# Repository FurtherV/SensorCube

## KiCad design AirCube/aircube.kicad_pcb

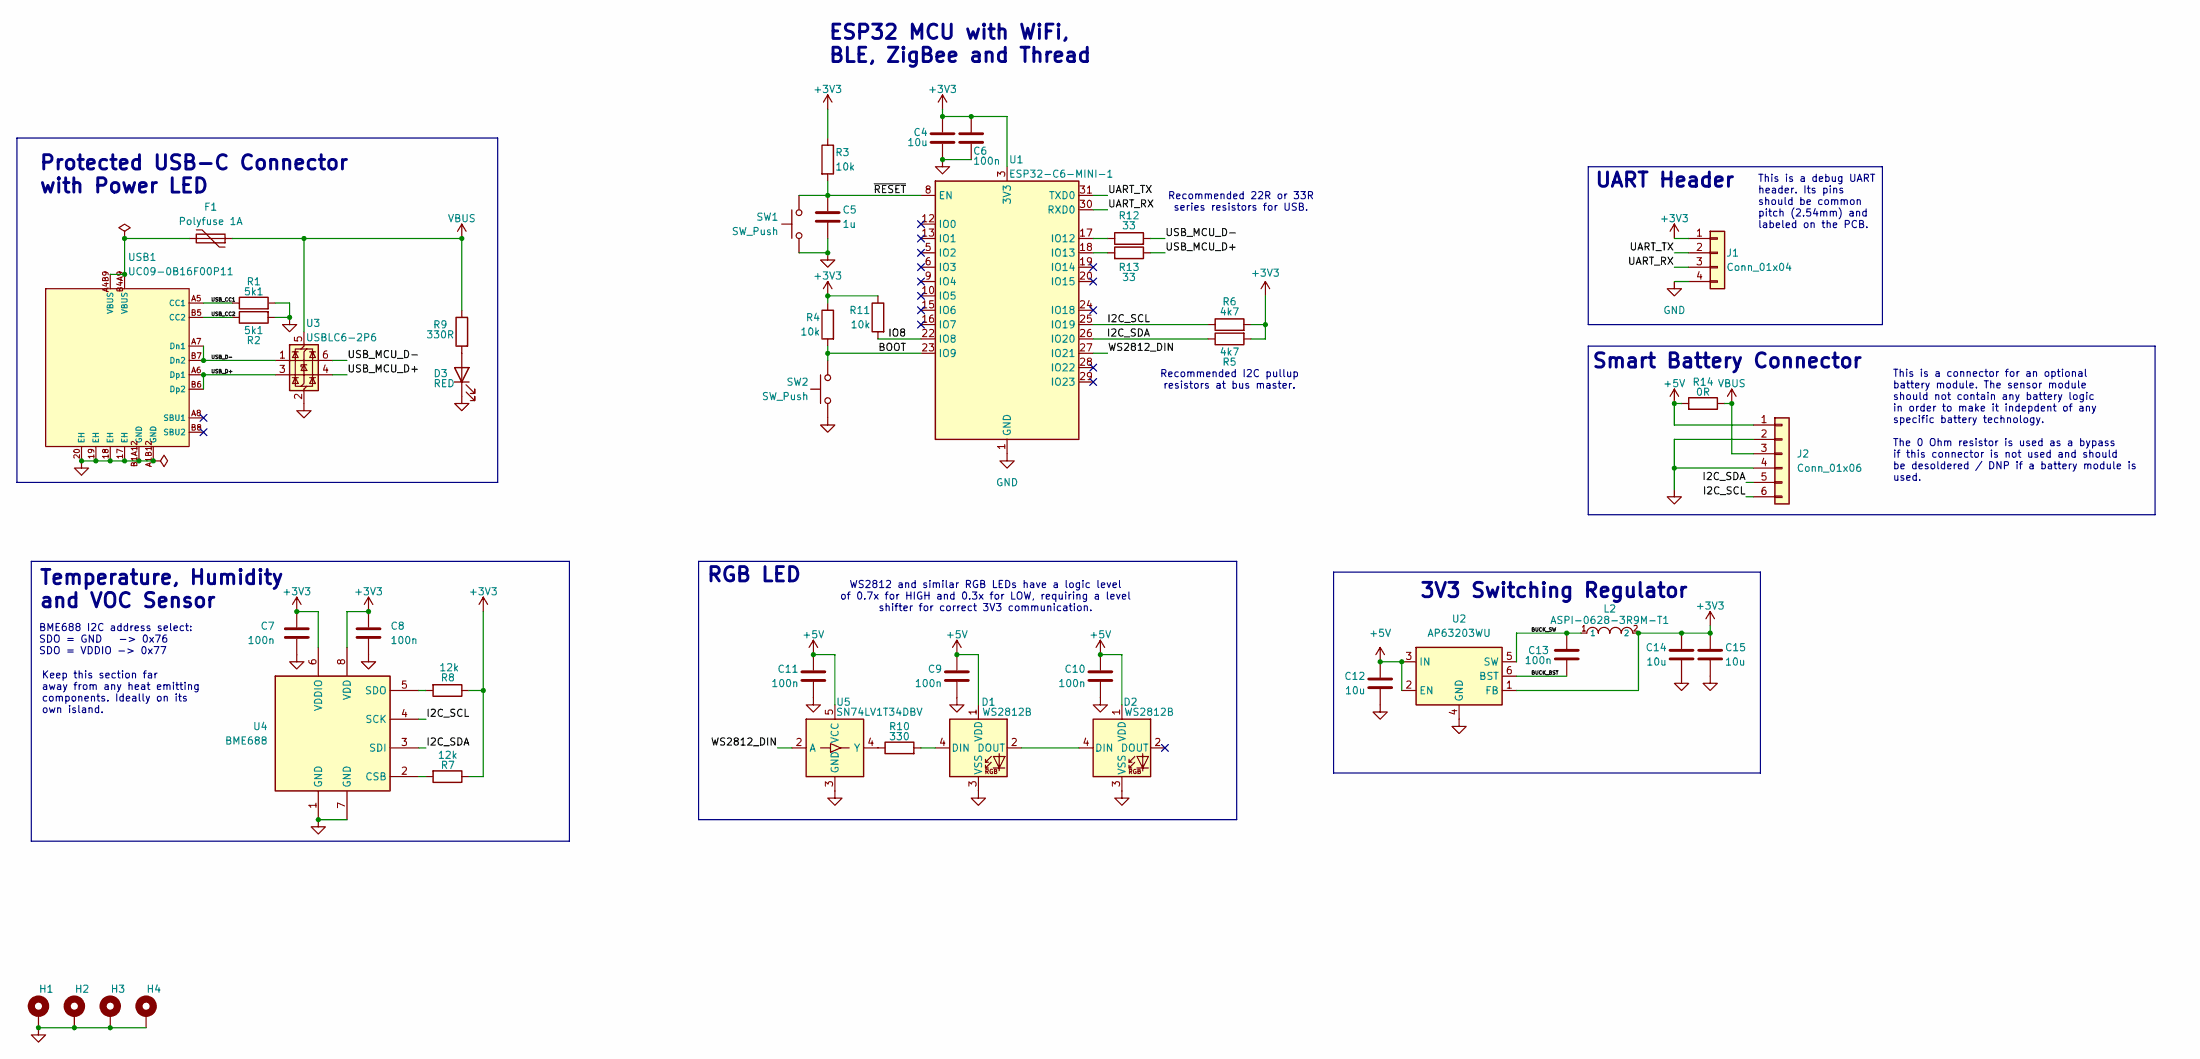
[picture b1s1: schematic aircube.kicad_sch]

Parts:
C4: 10u; C_0603_1608Metric
C5: 1u; C_0603_1608Metric
C6, C7, C8, C9, C10, C11, C13: 100n; C_0603_1608Metric
C12, C14, C15: 10u; C_0805_2012Metric
D1, D2: WS2812B; LED_WS2812B_PLCC4_5.0x5.0mm_P3.2mm
D3: RED; LED_0603_1608Metric
F1: Polyfuse 1A; Fuse_1812_4532Metric
H1, H2, H3, H4: MountingHole_Pad; MountingHole_2.2mm_M2_Pad
J1: Conn_01x04; PinHeader_1x04_P2.54mm_Vertical
J2: Conn_01x06; JST_PH_B6B-PH-K_1x06_P2.00mm_Vertical
L2: ASPI-0628-3R9M-T1; C5570229_IND-SMD_L6_0-W6_0; LCSC C5570229
R1, R2: 5k1; R_0603_1608Metric
R3, R4, R11: 10k; R_0603_1608Metric
R5, R6: 4k7; R_0603_1608Metric
R7, R8: 12k; R_0603_1608Metric
R9: 330R; R_0603_1608Metric
R10: 330; R_0603_1608Metric
R12, R13: 33; R_0603_1608Metric
R14: 0R; R_0805_2012Metric_Pad1.20x1.40mm_HandSolder
SW1, SW2: SW_Push
U1: ESP32-C6-MINI-1
U2: AP63203WU; TSOT-23-6
U3: USBLC6-2P6; SOT-666
U4: BME688; Bosch_LGA-8_3x3mm_P0.8mm_ClockwisePinNumbering
U5: SN74LV1T34DBV; SOT-23-5
USB1: UC09-0B16F00P11; C36936538_USB-C_UC09-0B16F00P11; LCSC C36936538

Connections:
+3V3: C4.1, C6.1, C7.1, C8.1, C14.1, C15.1, J1.1, L2.2, R3.1, R4.1, R5.2, R6.2, R7.1, R8.1, R11.1, U1.3 (3V3), U2.1 (FB), U4.6 (VDDIO), U4.8 (VDD)
+5V: C9.1, C10.1, C11.1, C12.1, D1.1 (VDD), D2.1 (VDD), J2.1, R14.2, U2.2 (EN), U2.3 (IN), U5.5 (VCC)
/BOOT: R4.2, SW2.1, U1.23 (IO9)
/BUCK_BST: C13.1, U2.6 (BST)
/BUCK_SW: C13.2, L2.1, U2.5 (SW)
/I2C_SCL: J2.6, R6.1, U1.25 (IO19), U4.4 (SCK)
/I2C_SDA: J2.5, R5.1, U1.26 (IO20), U4.3 (SDI)
/IO8: R11.2, U1.22 (IO8)
/UART_RX: J1.3, U1.30 (RXD0)
/UART_TX: J1.2, U1.31 (TXD0)
/USB_CC1: R1.1, USB1.A5 (CC1)
/USB_CC2: R2.1, USB1.B5 (CC2)
/USB_D+: U3.3 (I/O2), USB1.A6 (Dp1), USB1.B6 (Dp2)
/USB_D-: U3.1 (I/O1), USB1.A7 (Dn1), USB1.B7 (Dn2)
/USB_MCU_D+: R13.1, U3.4 (I/O2)
/USB_MCU_D-: R12.2, U3.6 (I/O1)
/WS2812_DIN: U1.27 (IO21), U5.2 (A)
/~RESET: C5.1, R3.2, SW1.1, U1.8 (EN)
GND: C4.2, C5.2, C6.2, C7.2, C8.2, C9.2, C10.2, C11.2, C12.2, C14.2, C15.2, D1.3 (VSS), D2.3 (VSS), D3.1 (K), H1.1 (1_1), H2.1 (1_1), H3.1 (1_1), H4.1 (1_1), J1.4, J2.2, J2.4, R1.2, R2.2, SW1.2, SW2.2, U1.1 (GND), U1.2 (GND), U1.11 (GND), U1.14 (GND), U1.36 (GND), U1.37 (GND), U1.38 (GND), U1.39 (GND), U1.40 (GND), U1.41 (GND), U1.42 (GND), U1.43 (GND), U1.44 (GND), U1.45 (GND), U1.46 (GND), U1.47 (GND), U1.48 (GND), U1.49 (GND), U1.50 (GND), U1.51 (GND), U1.52 (GND), U1.53 (GND), U2.4 (GND), U3.2 (GND), U4.1 (GND), U4.7 (GND), U5.3 (GND), USB1.17 (EH), USB1.18 (EH), USB1.19 (EH), USB1.20 (EH), USB1.A1B12 (GND), USB1.B1A12 (GND)
unnamed: D1.4 (DIN), R10.2
unnamed: D1.2 (DOUT), D2.4 (DIN)
unnamed: D3.2 (A), R9.2
unnamed: F1.2, USB1.A4B9 (VBUS), USB1.B4A9 (VBUS)
unnamed: R12.1, U1.17 (IO12)
unnamed: R13.2, U1.18 (IO13)
unnamed: R7.2, U4.2 (CSB)
unnamed: R8.2, U4.5 (SDO)
unnamed: R10.1, U5.4 (Y)
VBUS: F1.1, J2.3, R9.1, R14.1, U3.5 (VBUS)

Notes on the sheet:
Smart Battery Connector
3V3 Switching Regulator
This is a connector for an optional battery module. The sensor module should not contain any battery logic in order to make it indepdent of any specific battery technology. The 0 Ohm resistor is used as a bypass if this connector is not used and should be desoldered / DNP if a battery module is use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
Recommended I2C pullup resistors at bus master.
WS2812 and similar RGB LEDs have a logic level of 0.7x for HIGH and 0.3x for LOW, requiring a level shifter for correct 3V3 communication.
Keep this section far away from any heat emitting components. Ideally on its own island.
Recommended 22R or 33R series resistors for USB.
Protected USB-C Connector with Power LED
Temperature, Humidity and VOC Sensor
ESP32 MCU with WiFi, BLE, ZigBee and Thread
RGB LED
BME688 I2C address select: SDO = GND -> 0x76 SDO = VDDIO -> 0x77
UART Header
This is a debug UART header. Its pins should be common pitch (2.54mm) and labeled on the PCB.

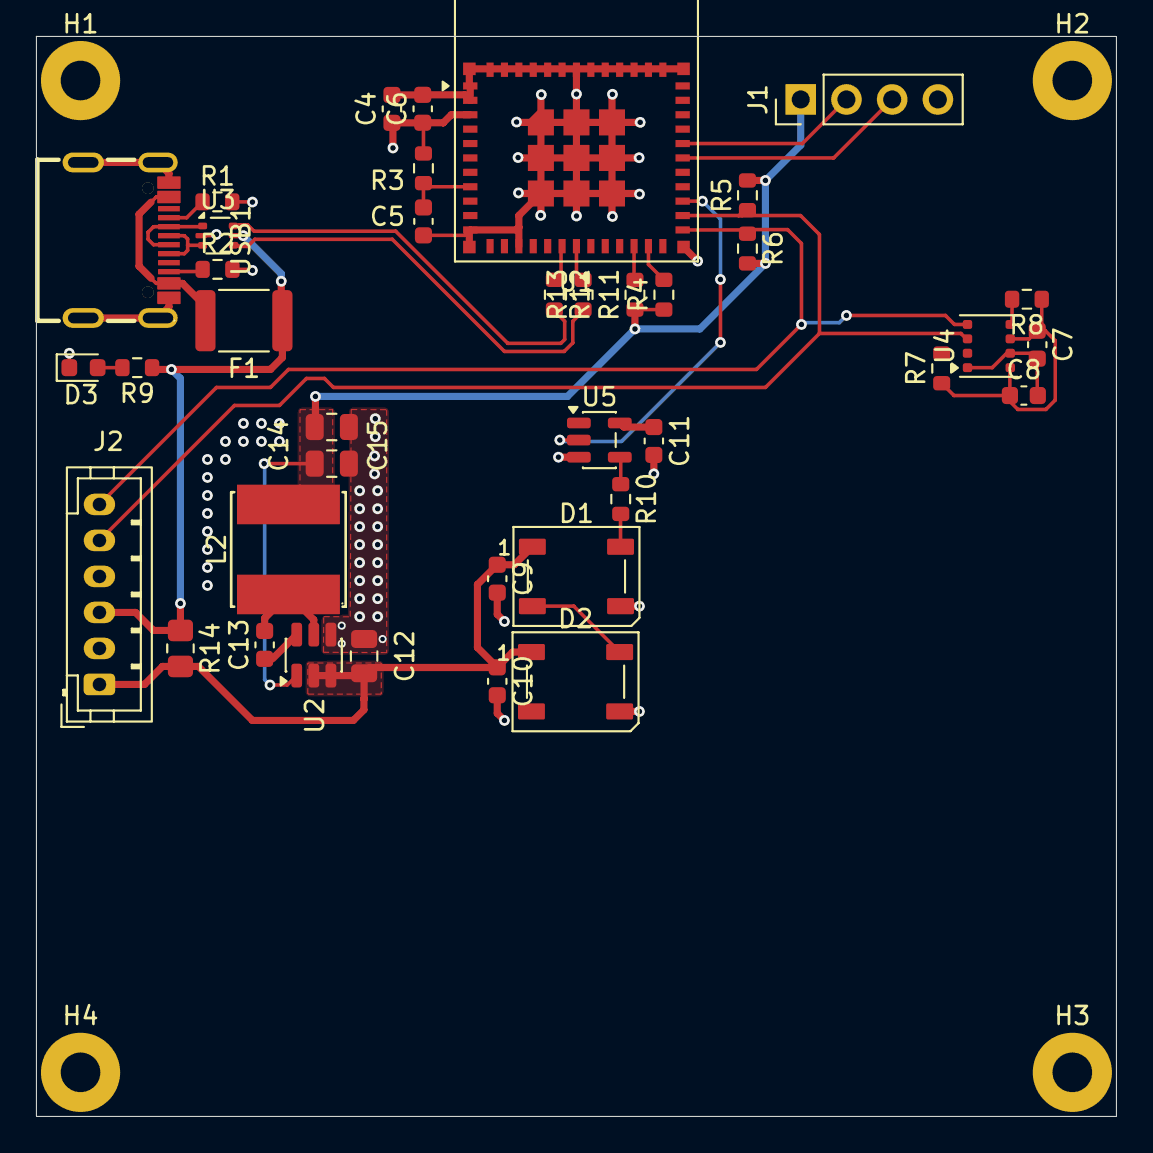
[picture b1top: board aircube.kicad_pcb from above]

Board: 4 copper layers, 60.0 x 60.0 mm, 43 parts (0 on the bottom side), 29 nets.
